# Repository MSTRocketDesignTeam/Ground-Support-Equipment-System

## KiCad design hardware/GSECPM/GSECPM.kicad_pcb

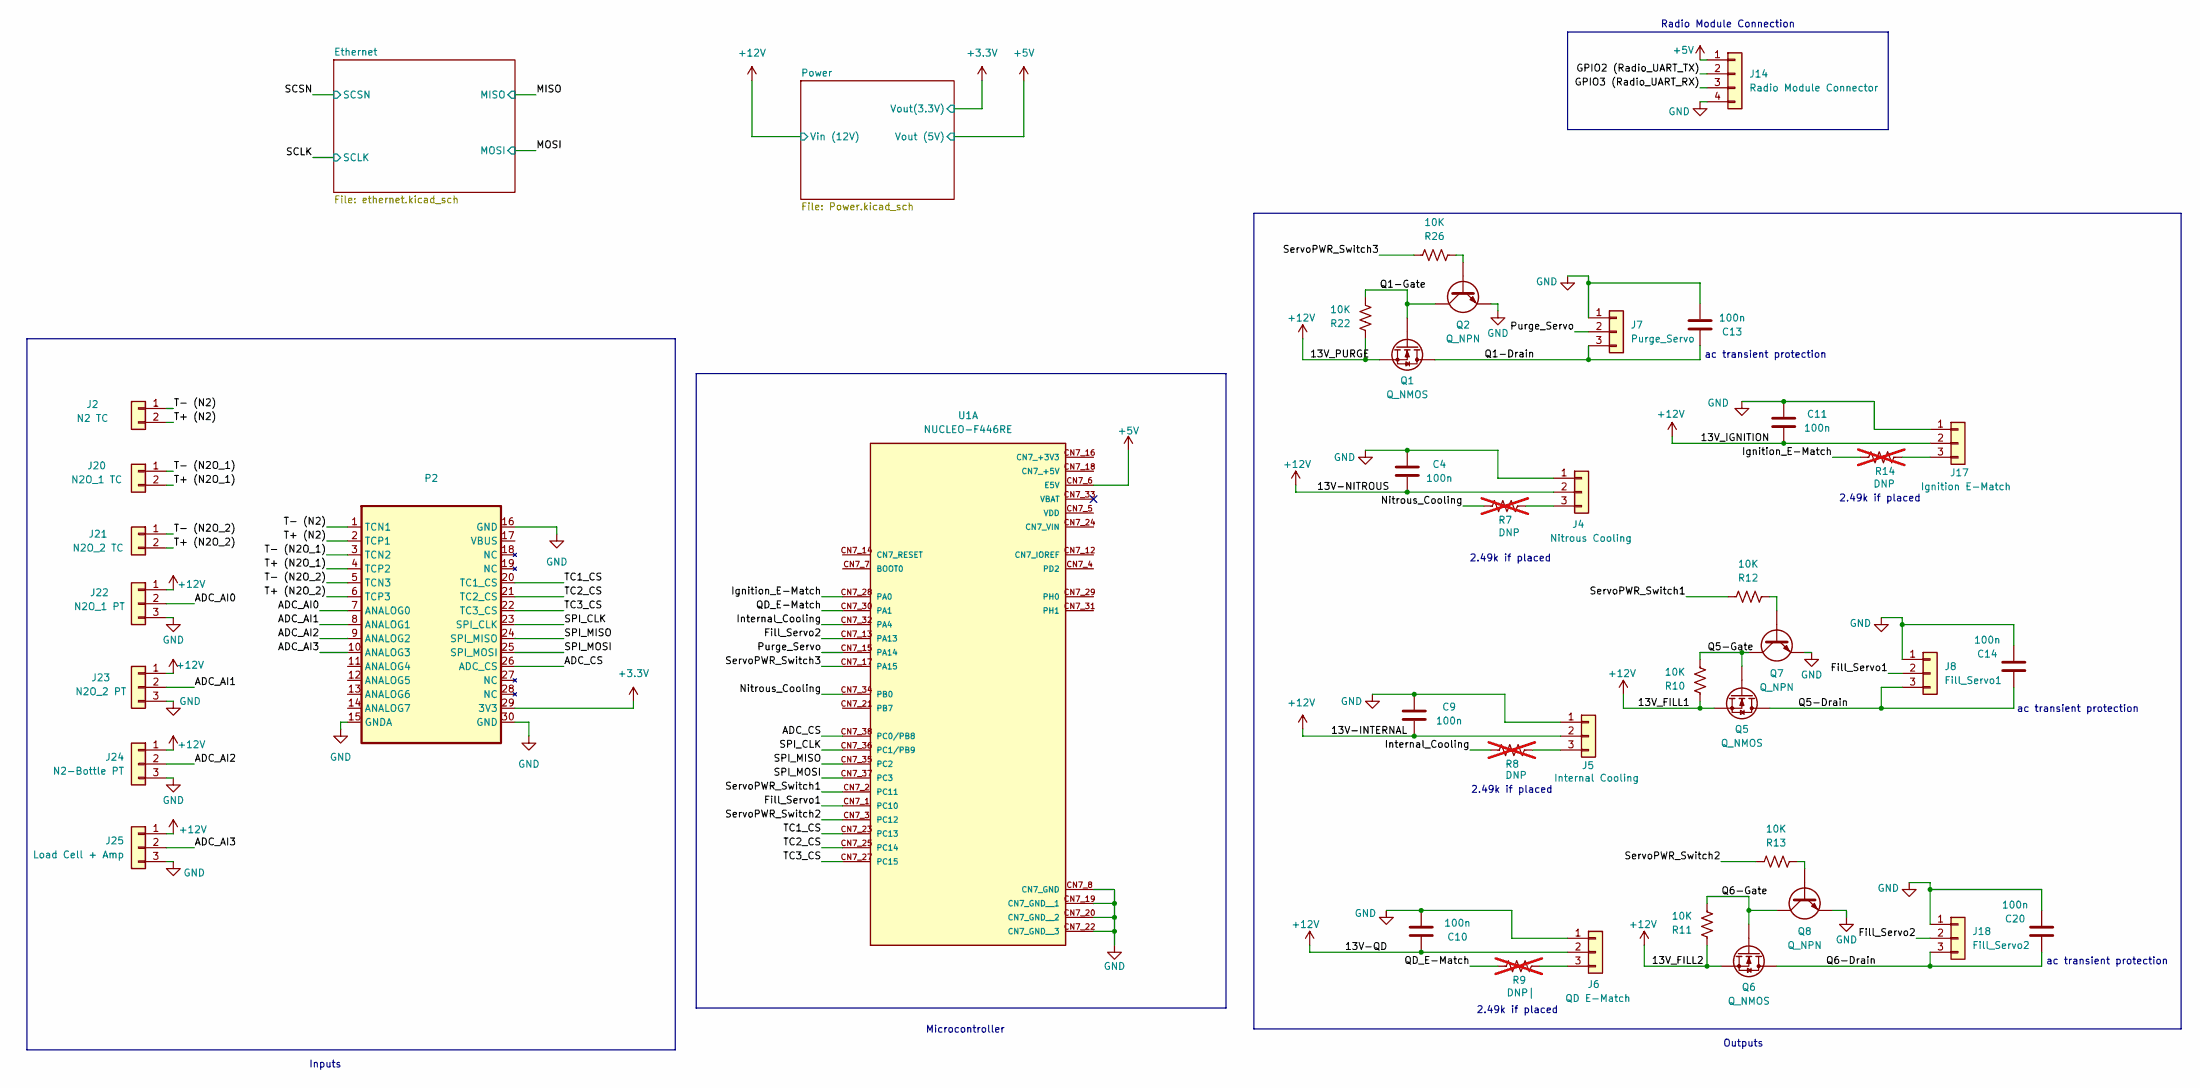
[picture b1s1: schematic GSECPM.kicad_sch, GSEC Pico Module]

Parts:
C4, C9, C10, C11, C13, C14, C20: 100n; C_0603_1608Metric
J2: N2 TC; TerminalBlock_Xinya_XY308-2.54-2P_1x02_P2.54mm_Horizontal
J4: Nitrous Cooling; PinHeader_1x03_P2.54mm_Vertical
J5: Internal Cooling; PinHeader_1x03_P2.54mm_Vertical
J6: QD E-Match; PinHeader_1x03_P2.54mm_Vertical
J7: Purge_Servo; TerminalBlock_Xinya_XY308-2.54-3P_1x03_P2.54mm_Horizontal
J8: Fill_Servo1; TerminalBlock_Xinya_XY308-2.54-3P_1x03_P2.54mm_Horizontal
J14: Radio Module Connector; PinHeader_1x04_P2.54mm_Vertical
J17: Ignition E-Match; PinHeader_1x03_P2.54mm_Vertical
J18: Fill_Servo2; TerminalBlock_Xinya_XY308-2.54-3P_1x03_P2.54mm_Horizontal
J20: N2O_1 TC; TerminalBlock_Xinya_XY308-2.54-2P_1x02_P2.54mm_Horizontal
J21: N2O_2 TC; TerminalBlock_Xinya_XY308-2.54-2P_1x02_P2.54mm_Horizontal
J22: N2O_1 PT; TerminalBlock_Xinya_XY308-2.54-3P_1x03_P2.54mm_Horizontal
J23: N2O_2 PT; TerminalBlock_Xinya_XY308-2.54-3P_1x03_P2.54mm_Horizontal
J24: N2-Bottle PT; TerminalBlock_Xinya_XY308-2.54-3P_1x03_P2.54mm_Horizontal
J25: Load Cell + Amp; TerminalBlock_Xinya_XY308-2.54-3P_1x03_P2.54mm_Horizontal
P2: DAQBoard V1
Q1, Q5, Q6: Q_NMOS; SOT-223_3P7X6P7_ONS
Q2, Q7, Q8: Q_NPN; SOT-323_SC-70
R7, R8, R14: DNP; R_0603_1608Metric; not fitted
R9: DNP|; R_0603_1608Metric; not fitted
R10, R11, R12, R13, R22, R26: 10K; R_0603_1608Metric
U1: NUCLEO-F446RE; MODULE_NUCLEO-F446RE; MPN NUCLEO-F446RE

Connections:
+3.3V: P2.29 (3V3); also elsewhere on the board
+5V: J14.1, U1.CN7_6 (E5V); also elsewhere on the board
+12V: C4.1, C9.1, C10.1, C11.1, J4.2, J5.2, J6.2, J17.2, J22.1, J23.1, J24.1, J25.1, Q1.3 (S), Q5.3 (S), Q6.3 (S), R10.2, R11.2, R22.2; also elsewhere on the board
/ADC_AI0: J22.2, P2.7 (ANALOG0)
/ADC_AI1: J23.2, P2.8 (ANALOG1)
/ADC_AI2: J24.2, P2.9 (ANALOG2)
/ADC_AI3: J25.2, P2.10 (ANALOG3)
/ADC_CS: P2.26 (ADC_CS), U1.CN7_38 (PC0/PB8)
/Fill_Servo1: J8.2, U1.CN7_1 (PC10)
/Fill_Servo2: J18.2, U1.CN7_13 (PA13)
/GPIO2 (Radio_UART_TX): J14.2
/GPIO3 (Radio_UART_RX): J14.3
/Ignition_E-Match: R14.1, U1.CN7_28 (PA0)
/Internal_Cooling: R8.1, U1.CN7_32 (PA4)
/Nitrous_Cooling: R7.1, U1.CN7_34 (PB0)
/Purge_Servo: J7.2, U1.CN7_15 (PA14)
/Q1-Drain: C13.1, J7.3, Q1.2 (D)
/Q1-Gate: Q1.1 (G), Q2.3 (C), R22.1
/Q5-Drain: C14.1, J8.3, Q5.2 (D)
/Q5-Gate: Q5.1 (G), Q7.3 (C), R10.1
/Q6-Drain: C20.1, J18.3, Q6.2 (D)
/Q6-Gate: Q6.1 (G), Q8.3 (C), R11.1
/QD_E-Match: R9.1, U1.CN7_30 (PA1)
/SPI_CLK: P2.23 (SPI_CLK), U1.CN7_36 (PC1/PB9)
/SPI_MISO: P2.24 (SPI_MISO), U1.CN7_35 (PC2)
/SPI_MOSI: P2.25 (SPI_MOSI), U1.CN7_37 (PC3)
/ServoPWR_Switch1: R12.2, U1.CN7_2 (PC11)
/ServoPWR_Switch2: R13.2, U1.CN7_3 (PC12)
/ServoPWR_Switch3: R26.2, U1.CN7_17 (PA15)
/T+ (N2): J2.2, P2.2 (TCP1)
/T+ (N2O_1): J20.2, P2.4 (TCP2)
/T+ (N2O_2): J21.2, P2.6 (TCP3)
/T- (N2): J2.1, P2.1 (TCN1)
/T- (N2O_1): J20.1, P2.3 (TCN2)
/T- (N2O_2): J21.1, P2.5 (TCN3)
/TC1_CS: P2.20 (TC1_CS), U1.CN7_23 (PC13)
/TC2_CS: P2.21 (TC2_CS), U1.CN7_25 (PC14)
/TC3_CS: P2.22 (TC3_CS), U1.CN7_27 (PC15)
GND: C4.2, C9.2, C10.2, C11.2, C13.2, C14.2, C20.2, J4.1, J5.1, J6.1, J7.1, J8.1, J14.4, J17.1, J18.1, J22.3, J23.3, J24.3, J25.3, P2.15 (GNDA), P2.16 (GND), P2.30 (GND), Q2.2 (E), Q7.2 (E), Q8.2 (E), U1.CN7_8 (CN7_GND), U1.CN7_19 (CN7_GND__1), U1.CN7_20 (CN7_GND__2), U1.CN7_22 (CN7_GND__3); also elsewhere on the board
unnamed: J4.3, R7.2
unnamed: J5.3, R8.2
unnamed: J6.3, R9.2
unnamed: J17.3, R14.2
unnamed: Q2.1 (B), R26.1
unnamed: Q7.1 (B), R12.1
unnamed: Q8.1 (B), R13.1

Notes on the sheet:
Outputs
ac transient protection
2.49k if placed
Radio Module Connection
Inputs
Microcontroller

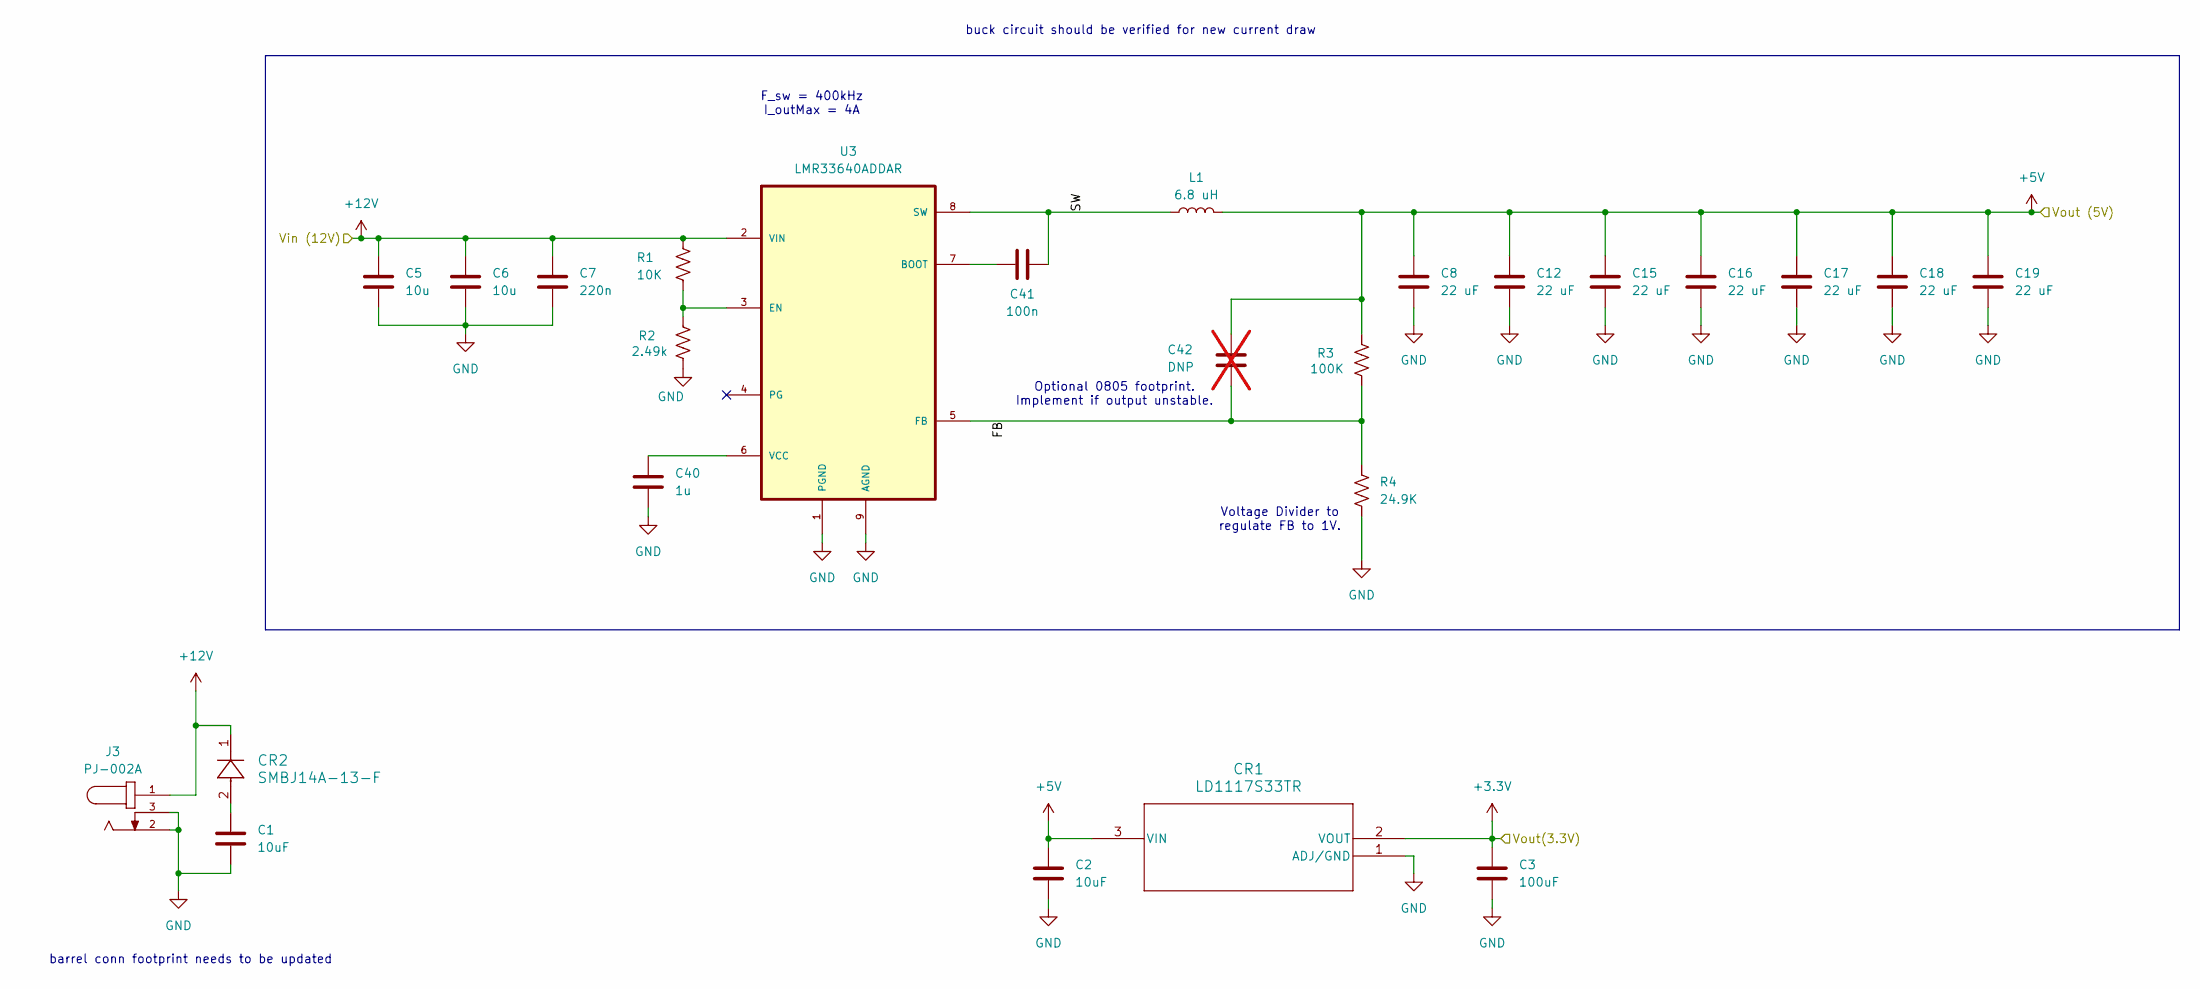
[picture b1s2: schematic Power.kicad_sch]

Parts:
C1, C2: 10uF; C_0603_1608Metric
C3: 100uF; C_1206_3216Metric
C5, C6: 10u; C_1210_3225Metric
C7: 220n; C_0805_2012Metric
C8, C12, C15, C16, C17, C18, C19: 22 uF; C_0805_2012Metric
C40: 1u; C_0805_2012Metric
C41: 100n; C_0603_1608Metric
C42: DNP; C_0805_2012Metric; not fitted
CR1: LD1117S33TR; SOT-223_STM
CR2: SMBJ14A-13-F; SMB_DIO
J3: PJ-002A; CUI_PJ-002A; MPN PJ-002A
L1: 6.8 uH; IND_BOURNS_SRR1260
R1: 10K; R_0603_1608Metric
R2: 2.49k; R_0603_1608Metric
R3: 100K; R_1210_3225Metric
R4: 24.9K; R_1210_3225Metric
U3: LMR33640ADDAR; Texas_HSOP-8-1EP_3.9x4.9mm_P1.27mm_ThermalVias

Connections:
+3.3V: C3.1, CR1.2 (VOUT); also elsewhere on the board
+5V: C2.1, C8.1, C12.1, C15.1, C16.1, C17.1, C18.1, C19.1, C42.2, CR1.3 (VIN), L1.2, R3.2; also elsewhere on the board
+12V: C5.1, C6.1, C7.1, CR2.1, J3.1, R1.1, U3.2 (VIN); also elsewhere on the board
/Power/FB: C42.1, R3.1, R4.1, U3.5 (FB)
/Power/SW: C41.2, L1.1, U3.8 (SW)
GND: C1.2, C2.2, C3.2, C5.2, C6.2, C7.2, C8.2, C12.2, C15.2, C16.2, C17.2, C18.2, C19.2, C40.2, CR1.1 (ADJ/GND), J3.2, J3.3, R2.1, R4.2, U3.1 (PGND), U3.9 (AGND); also elsewhere on the board
unnamed: C1.1, CR2.2
unnamed: C41.1, U3.7 (BOOT)
unnamed: R1.2, R2.2, U3.3 (EN)
unnamed: C40.1, U3.6 (VCC)

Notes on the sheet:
F_sw = 400kHz I_outMax = 4A
Optional 0805 footprint. Implement if output unstable.
Voltage Divider to regulate FB to 1V.
buck circuit should be verified for new current draw
barrel conn footprint needs to be updated

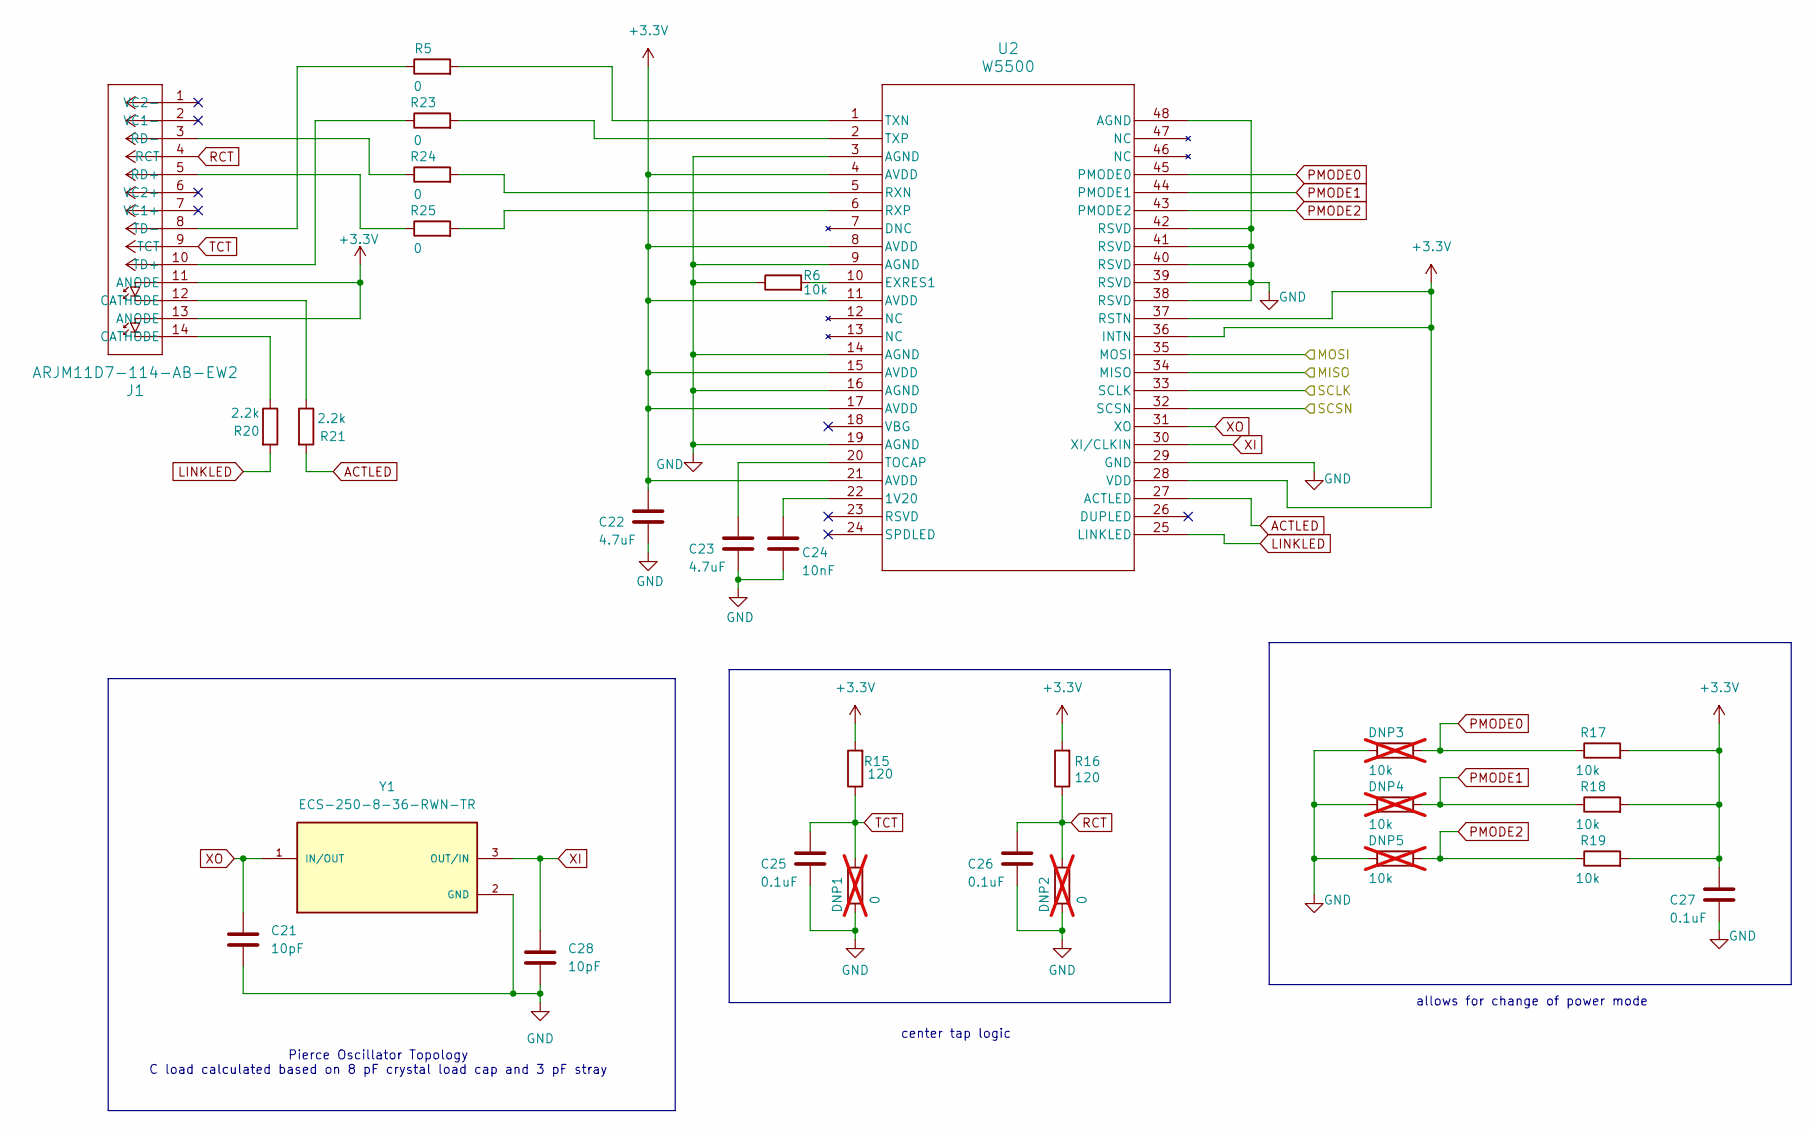
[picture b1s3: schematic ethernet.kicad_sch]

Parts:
C21, C28: 10pF; C_0603_1608Metric
C22, C23: 4.7uF; C_0603_1608Metric
C24: 10nF; C_0603_1608Metric
C25, C26, C27: 0.1uF; C_0603_1608Metric
DNP1, DNP2: 0; R_0805_2012Metric; not fitted
DNP3, DNP4, DNP5: 10k; R_0805_2012Metric; not fitted
J1: ARJM11D7-114-AB-EW2; CONN_ARJM11D7-114-AB-EW2_ABR
R5, R23, R24, R25: 0; R_0603_1608Metric
R6, R17, R18, R19: 10k; R_0603_1608Metric
R15, R16: 120; R_0603_1608Metric
R20, R21: 2.2k; R_0603_1608Metric
U2: W5500; 48LQFP_W5500_WIZ
Y1: ECS-250-8-36-RWN-TR; XTAL_ECS-250-8-36-RWN-TR; PARTREV 2017

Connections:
+3.3V: C22.1, C27.1, J1.11 (ANODE), J1.13 (ANODE), R15.2, R16.2, R17.2, R18.2, R19.2, U2.4 (AVDD), U2.8 (AVDD), U2.11 (AVDD), U2.15 (AVDD), U2.17 (AVDD), U2.21 (AVDD), U2.28 (VDD), U2.36 (INTN), U2.37 (RSTN); also elsewhere on the board
/MISO: U2.34 (MISO)
/MOSI: U2.35 (MOSI)
/SCLK: U2.33 (SCLK)
/SCSN: U2.32 (SCSN)
ACTLED: R21.2, U2.27 (ACTLED)
GND: C21.2, C22.2, C23.2, C24.2, C25.2, C26.2, C27.2, C28.2, DNP1.1, DNP2.1, DNP3.1, DNP4.1, DNP5.1, R6.1, U2.3 (AGND), U2.9 (AGND), U2.14 (AGND), U2.16 (AGND), U2.19 (AGND), U2.29 (GND), U2.38 (RSVD), U2.39 (RSVD), U2.40 (RSVD), U2.41 (RSVD), U2.42 (RSVD), U2.48 (AGND), Y1.2 (GND); also elsewhere on the board
LINKLED: R20.2, U2.25 (LINKLED)
unnamed: J1.12 (CATHODE), R21.1
unnamed: J1.14 (CATHODE), R20.1
unnamed: J1.5 (RD+), R25.1
unnamed: J1.3 (RD-), R24.1
unnamed: J1.10 (TD+), R23.1
unnamed: J1.8 (TD-), R5.1
unnamed: C24.1, U2.22 (1V20)
unnamed: R6.2, U2.10 (EXRES1)
unnamed: R24.2, U2.5 (RXN)
unnamed: R25.2, U2.6 (RXP)
unnamed: C23.1, U2.20 (TOCAP)
unnamed: R5.2, U2.1 (TXN)
unnamed: R23.2, U2.2 (TXP)
PMODE0: DNP3.2, R17.1, U2.45 (PMODE0)
PMODE1: DNP4.2, R18.1, U2.44 (PMODE1)
PMODE2: DNP5.2, R19.1, U2.43 (PMODE2)
RCT: C26.1, DNP2.2, J1.4 (RCT), R16.1
TCT: C25.1, DNP1.2, J1.9 (TCT), R15.1
XI: C28.1, U2.30 (XI/CLKIN), Y1.3 (OUT/IN)
XO: C21.1, U2.31 (XO), Y1.1 (IN/OUT)

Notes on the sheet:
Pierce Oscillator Topology C load calculated based on 8 pF crystal load cap and 3 pF stray
center tap logic
allows for change of power mode

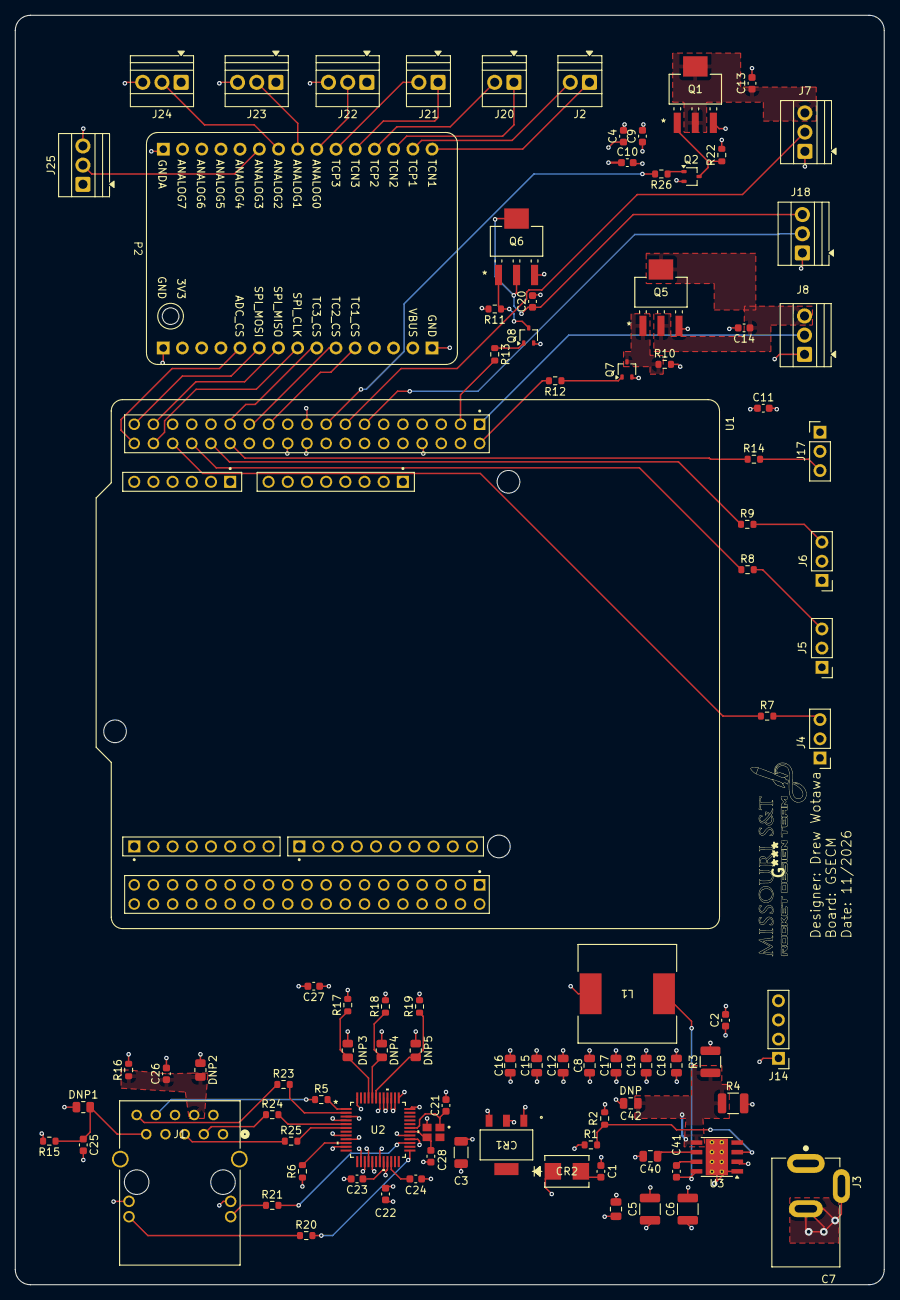
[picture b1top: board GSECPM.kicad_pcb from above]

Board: 4 copper layers, 115.0 x 168.0 mm, 93 parts (0 on the bottom side), 72 nets.

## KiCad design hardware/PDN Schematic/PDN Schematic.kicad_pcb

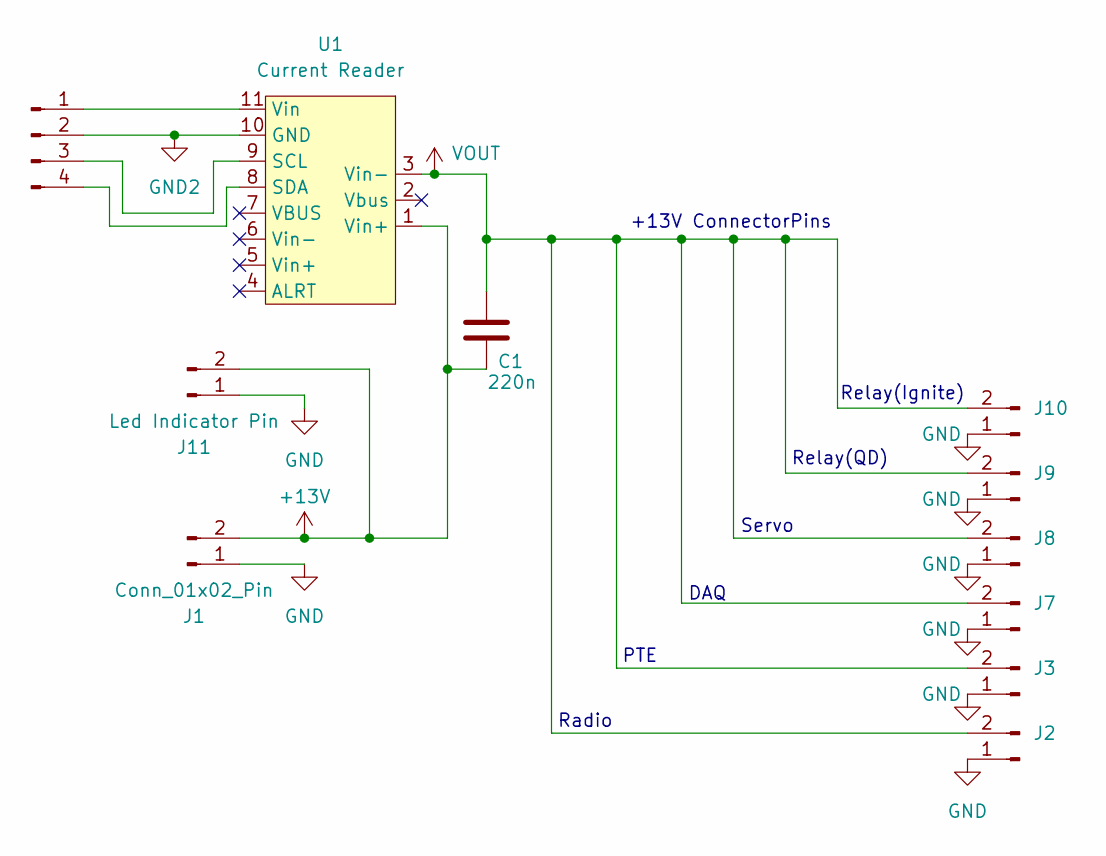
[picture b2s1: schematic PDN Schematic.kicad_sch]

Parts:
C1: 220n; C_0805_2012Metric; DigiKey Digikey: https://www.digikey.com/en/pro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
J1: Conn_01x02_Pin; AMASS_XT60-M_1x02_P7.20mm_Vertical
J2, J3, J7, J8, J9, J10: Conn_01x02_Pin; AMASS_XT30U-M_1x02_P5.0mm_Vertical
J4: Conn_01x04_Pin; PinHeader_1x04_P2.54mm_Vertical
J11: Led Indicator Pin; AMASS_XT30U-M_1x02_P5.0mm_Vertical
U1: Current Reader; INA238_MODULE

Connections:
+13V: C1.2, J1.2, J11.2, U1.1 (Vin+)
GND: J1.1, J2.1, J3.1, J7.1, J8.1, J9.1, J10.1, J11.1
GND2: J4.2, U1.10 (GND)
unnamed: J4.1, U1.11 (Vin)
unnamed: J4.3, U1.9 (SCL)
unnamed: J4.4, U1.8 (SDA)
VOUT: C1.1, J2.2, J3.2, J7.2, J8.2, J9.2, J10.2, U1.3 (Vin-)

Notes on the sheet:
Relay(Ignite)
Servo
Radio
Relay(QD)
+13V ConnectorPins
DAQ
PTE

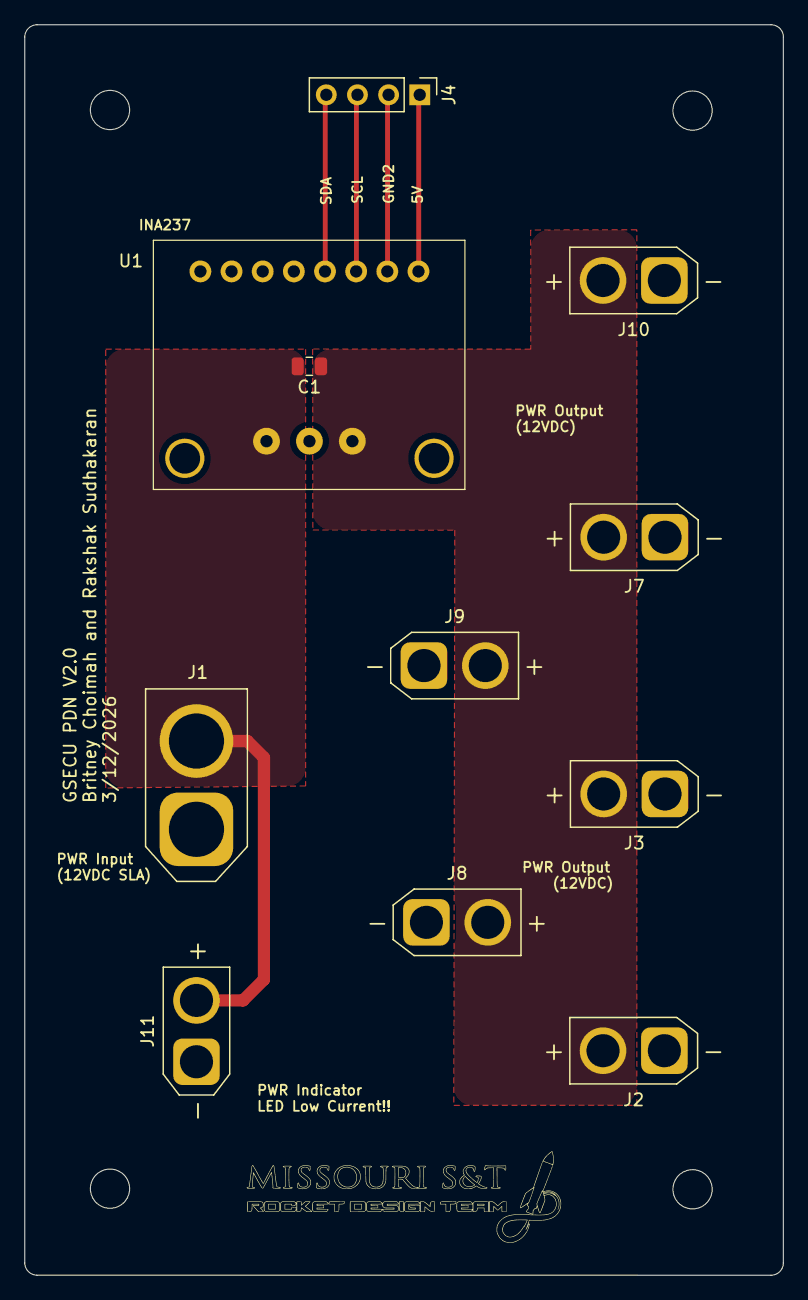
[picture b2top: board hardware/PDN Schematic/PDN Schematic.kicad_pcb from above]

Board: 2 copper layers, 61.9 x 102.0 mm, 11 parts (0 on the bottom side), 7 nets.

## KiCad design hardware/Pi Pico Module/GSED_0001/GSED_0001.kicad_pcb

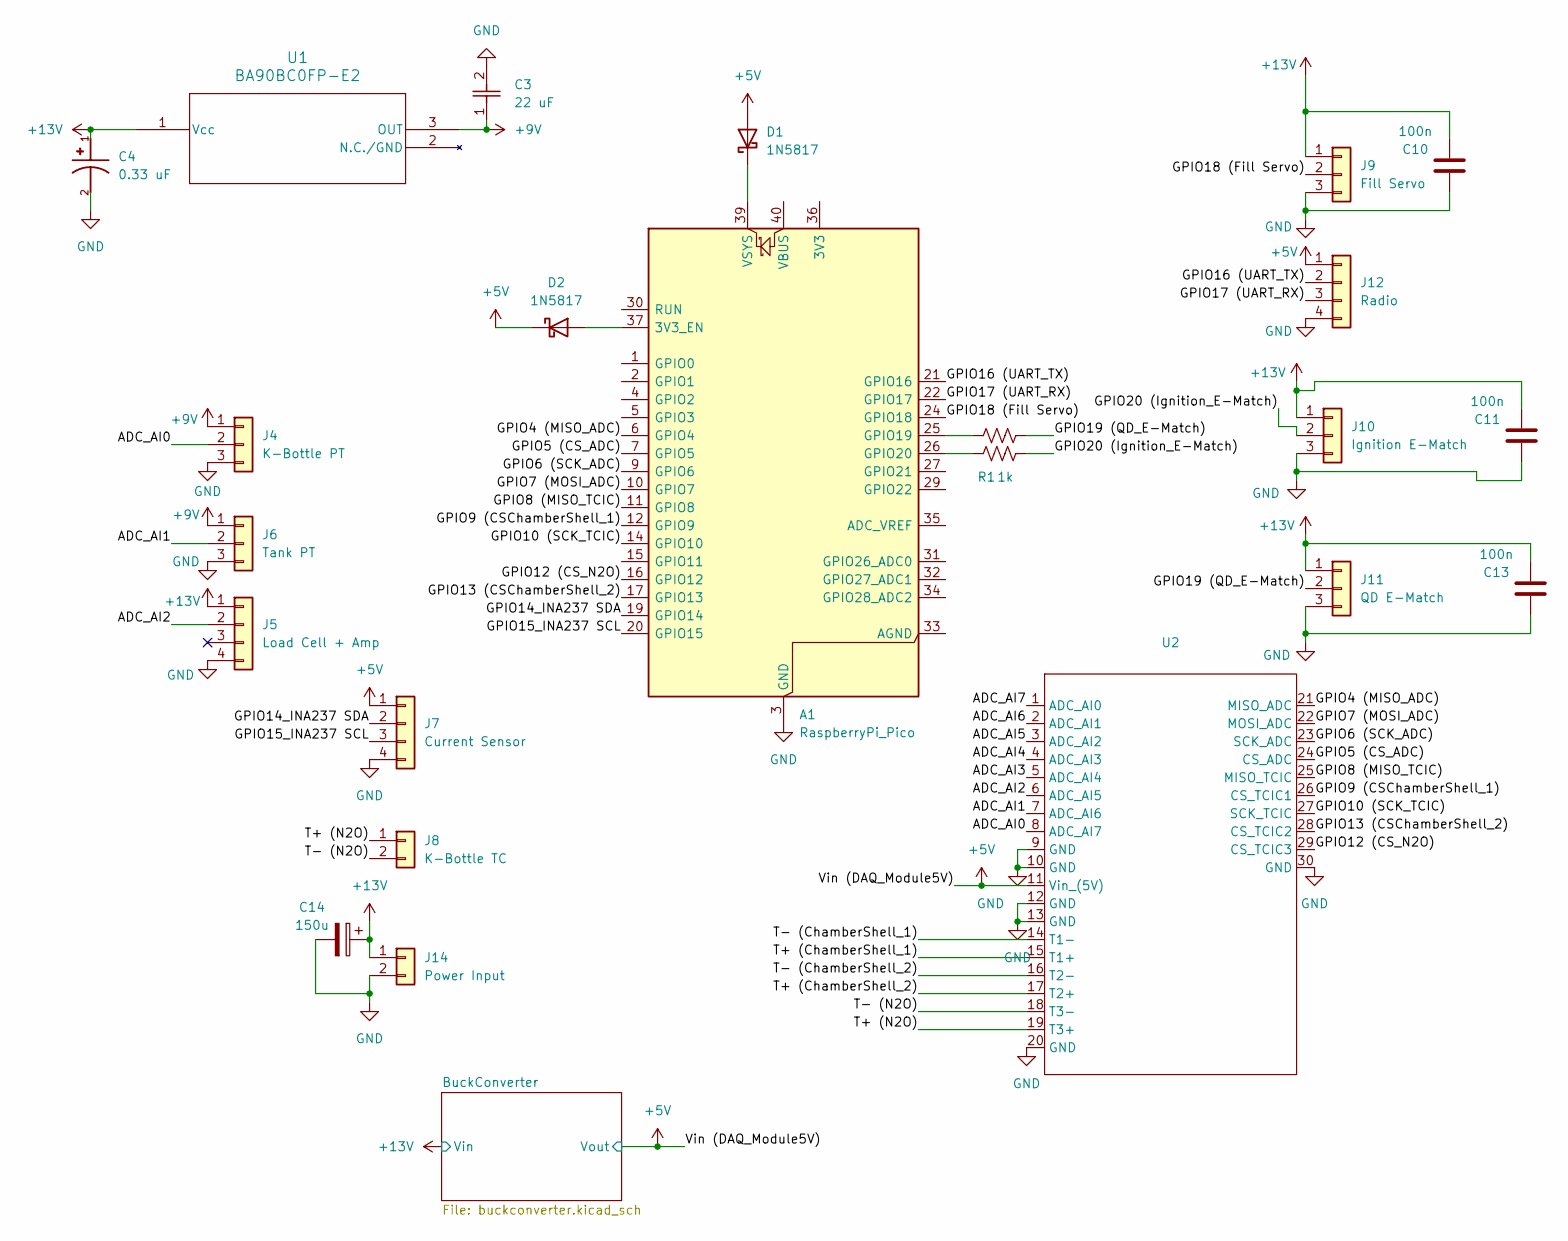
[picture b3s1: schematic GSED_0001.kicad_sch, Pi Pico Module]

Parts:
A1: RaspberryPi_Pico; RaspberryPi_Pico_Common_Unspecified
C3: 22 uF; C_0805_2012Metric
C4: 0.33 uF; CAPMP3216X180N; PARTREV 031320
C10, C11, C13: 100n; C_0603_1608Metric
C14: 150u; CAPPRD500W60D1000H1600
D1, D2: 1N5817; D_DO-41_SOD81_P10.16mm_Horizontal
J4: K-Bottle PT; PinHeader_1x03_P2.54mm_Vertical
J5: Load Cell + Amp; PinHeader_1x04_P2.54mm_Vertical
J6: Tank PT; PinHeader_1x03_P2.54mm_Vertical
J7: Current Sensor; PinHeader_1x04_P2.54mm_Vertical
J8: K-Bottle TC; AMKPCB
J9: Fill Servo; PinHeader_1x03_P2.54mm_Vertical
J10: Ignition E-Match; PinHeader_1x03_P2.54mm_Vertical
J11: QD E-Match; PinHeader_1x03_P2.54mm_Vertical
J12: Radio; PinHeader_1x04_P2.54mm_Vertical
J14: Power Input; AMASS_XT30U-M_1x02_P5.0mm_Vertical
R1, R2: 1k; R_0603_1608Metric
U1: BA90BC0FP-E2; TO252-3_ROM
U2: DAQ_Module

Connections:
+5V: D1.2 (A), D2.1 (K), J7.1, J12.1, U2.11 (Vin_(5V)); also elsewhere on the board
+9V: C3.1, J4.1, J6.1, U1.3 (OUT)
+13V: C4.1, C10.2, C11.2, C13.2, C14.1, J5.1, J9.1, J10.1, J11.1, J14.1, U1.1 (Vcc); also elsewhere on the board
/ADC_AI0: J4.2, U2.8 (ADC_AI7)
/ADC_AI1: J6.2, U2.7 (ADC_AI6)
/ADC_AI2: J5.2, U2.6 (ADC_AI5)
/ADC_AI3: U2.5 (ADC_AI4)
/ADC_AI4: U2.4 (ADC_AI3)
/ADC_AI5: U2.3 (ADC_AI2)
/ADC_AI6: U2.2 (ADC_AI1)
/ADC_AI7: U2.1 (ADC_AI0)
/GPIO4 (MISO_ADC): A1.6 (GPIO4), U2.21 (MISO_ADC)
/GPIO5 (CS_ADC): A1.7 (GPIO5), U2.24 (CS_ADC)
/GPIO6 (SCK_ADC): A1.9 (GPIO6), U2.23 (SCK_ADC)
/GPIO7 (MOSI_ADC): A1.10 (GPIO7), U2.22 (MOSI_ADC)
/GPIO8 (MISO_TCIC): A1.11 (GPIO8), U2.25 (MISO_TCIC)
/GPIO9 (CSChamberShell_1): A1.12 (GPIO9), U2.26 (CS_TCIC1)
/GPIO10 (SCK_TCIC): A1.14 (GPIO10), U2.27 (SCK_TCIC)
/GPIO12 (CS_N2O): A1.16 (GPIO12), U2.29 (CS_TCIC3)
/GPIO13 (CSChamberShell_2): A1.17 (GPIO13), U2.28 (CS_TCIC2)
/GPIO14_INA237 SDA: A1.19 (GPIO14), J7.2
/GPIO15_INA237 SCL: A1.20 (GPIO15), J7.3
/GPIO16 (UART_TX): A1.21 (GPIO16), J12.2
/GPIO17 (UART_RX): A1.22 (GPIO17), J12.3
/GPIO18 (Fill Servo): A1.24 (GPIO18), J9.2
/GPIO19 (QD_E-Match): J11.2, R2.1
/GPIO20 (Ignition_E-Match): J10.2, R1.1
/T+ (ChamberShell_1): U2.15 (T1+)
/T+ (ChamberShell_2): U2.17 (T2+)
/T+ (N2O): J8.1, U2.19 (T3+)
/T- (ChamberShell_1): U2.14 (T1-)
/T- (ChamberShell_2): U2.16 (T2-)
/T- (N2O): J8.2, U2.18 (T3-)
GND: A1.3 (GND), A1.8 (GND), A1.13 (GND), A1.18 (GND), A1.23 (GND), A1.28 (GND), A1.38 (GND), C3.2, C4.2, C10.1, C11.1, C13.1, C14.2, J4.3, J5.4, J6.3, J7.4, J9.3, J10.3, J11.3, J12.4, J14.2, U2.9 (GND), U2.10 (GND), U2.12 (GND), U2.13 (GND), U2.20 (GND), U2.30 (GND); also elsewhere on the board
unnamed: A1.37 (3V3_EN), D2.2 (A)
unnamed: A1.25 (GPIO19), R2.2
unnamed: A1.26 (GPIO20), R1.2
unnamed: A1.39 (VSYS), D1.1 (K)

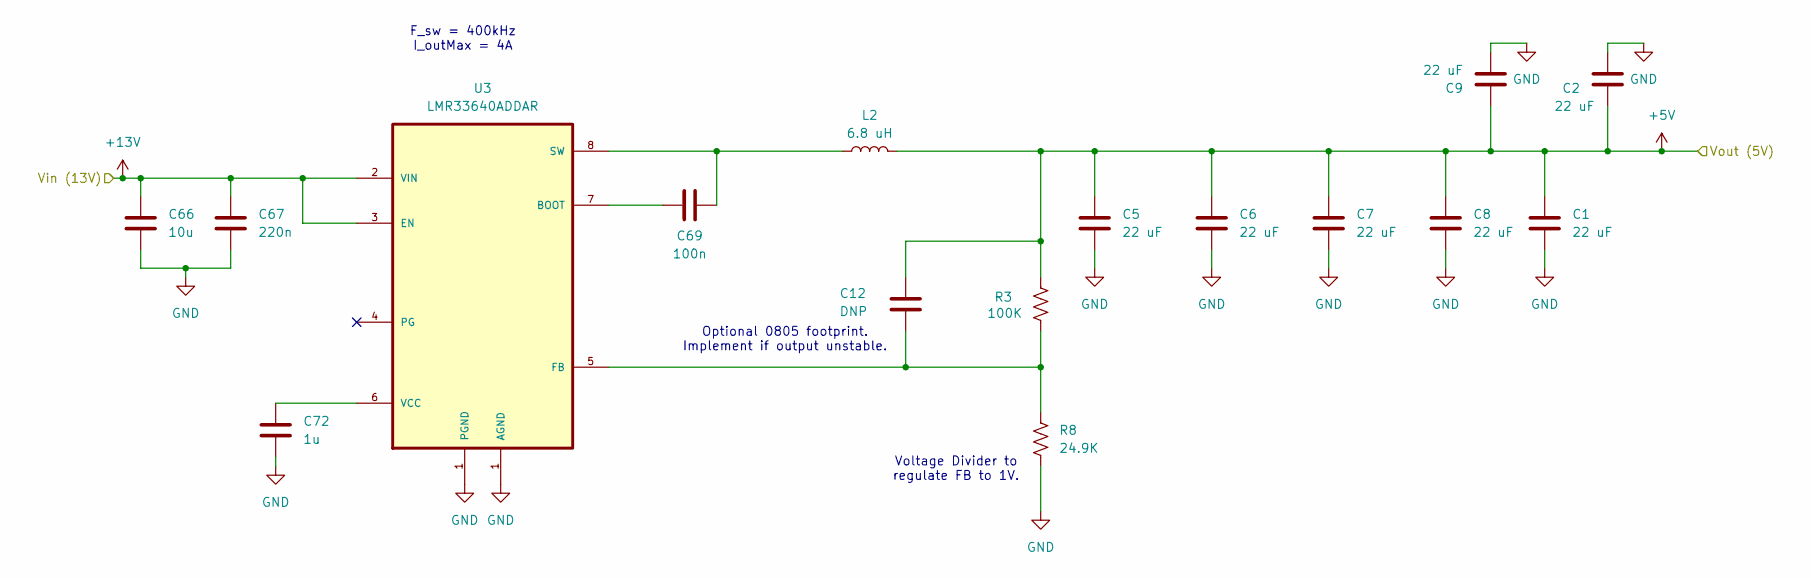
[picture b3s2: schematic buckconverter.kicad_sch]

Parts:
C1, C2, C5, C6, C7, C8, C9: 22 uF; C_0805_2012Metric
C12: DNP; C_0805_2012Metric
C66: 10u; C_0805_2012Metric
C67: 220n; C_0805_2012Metric
C69: 100n; C_0603_1608Metric
C72: 1u; C_0805_2012Metric
L2: 6.8 uH; IND_CSBX0650-6R8M
R3: 100K; R_0603_1608Metric
R8: 24.9K; R_0603_1608Metric
U3: LMR33640ADDAR; Texas_HSOP-8-1EP_3.9x4.9mm_P1.27mm_ThermalVias

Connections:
+5V: C1.1, C2.1, C5.1, C6.1, C7.1, C8.1, C9.1, C12.2, L2.2, R3.2; also elsewhere on the board
+13V: C66.1, C67.1, U3.2 (VIN), U3.3 (EN); also elsewhere on the board
GND: C1.2, C2.2, C5.2, C6.2, C7.2, C8.2, C9.2, C66.2, C67.2, C72.2, R8.2, U3.1 (PGND); also elsewhere on the board
unnamed: C69.1, U3.7 (BOOT)
unnamed: C12.1, R3.1, R8.1, U3.5 (FB)
unnamed: C69.2, L2.1, U3.8 (SW)
unnamed: C72.1, U3.6 (VCC)

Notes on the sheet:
Optional 0805 footprint. Implement if output unstable.
Voltage Divider to regulate FB to 1V.
F_sw = 400kHz I_outMax = 4A

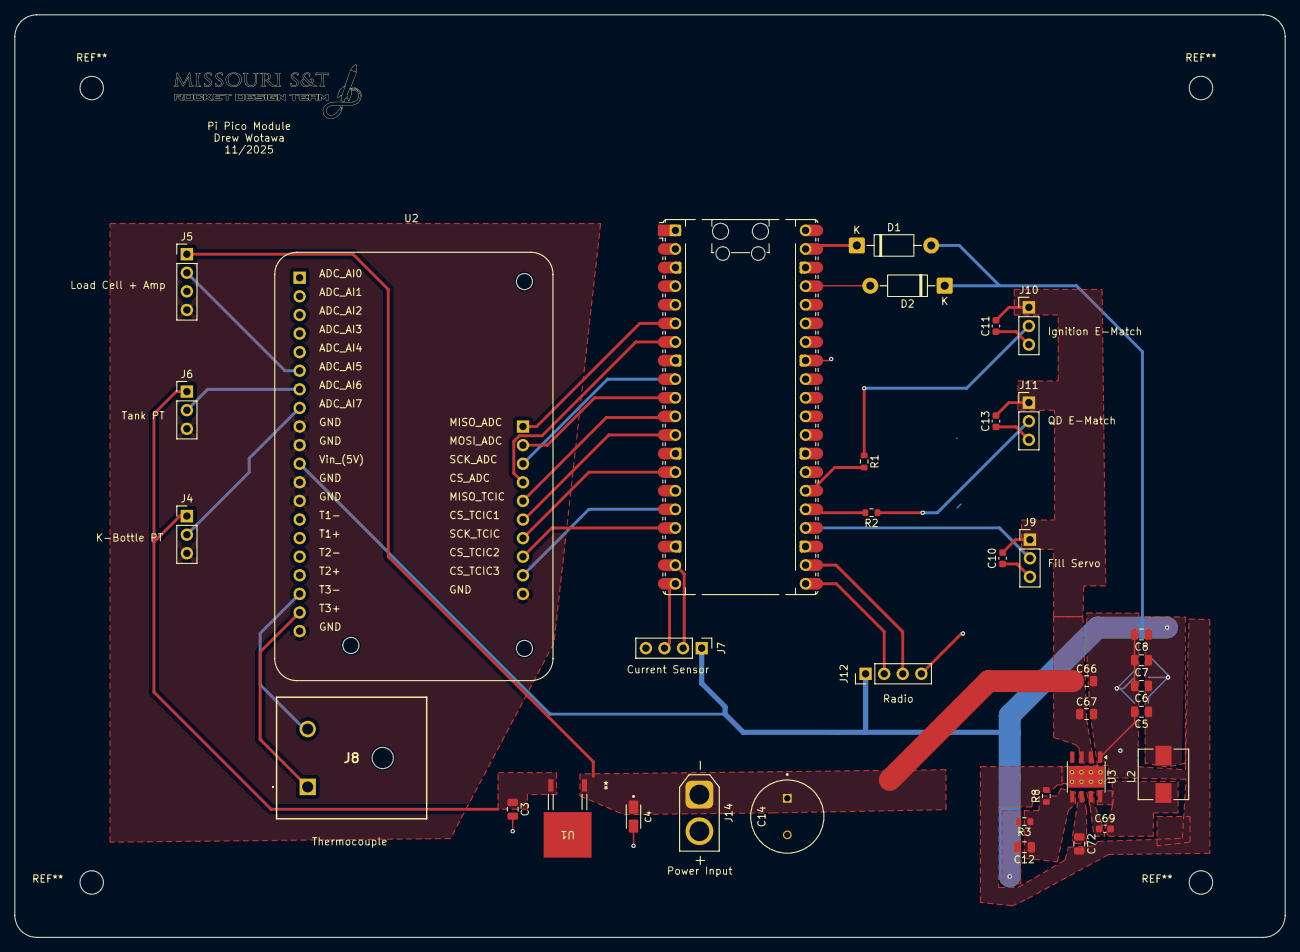
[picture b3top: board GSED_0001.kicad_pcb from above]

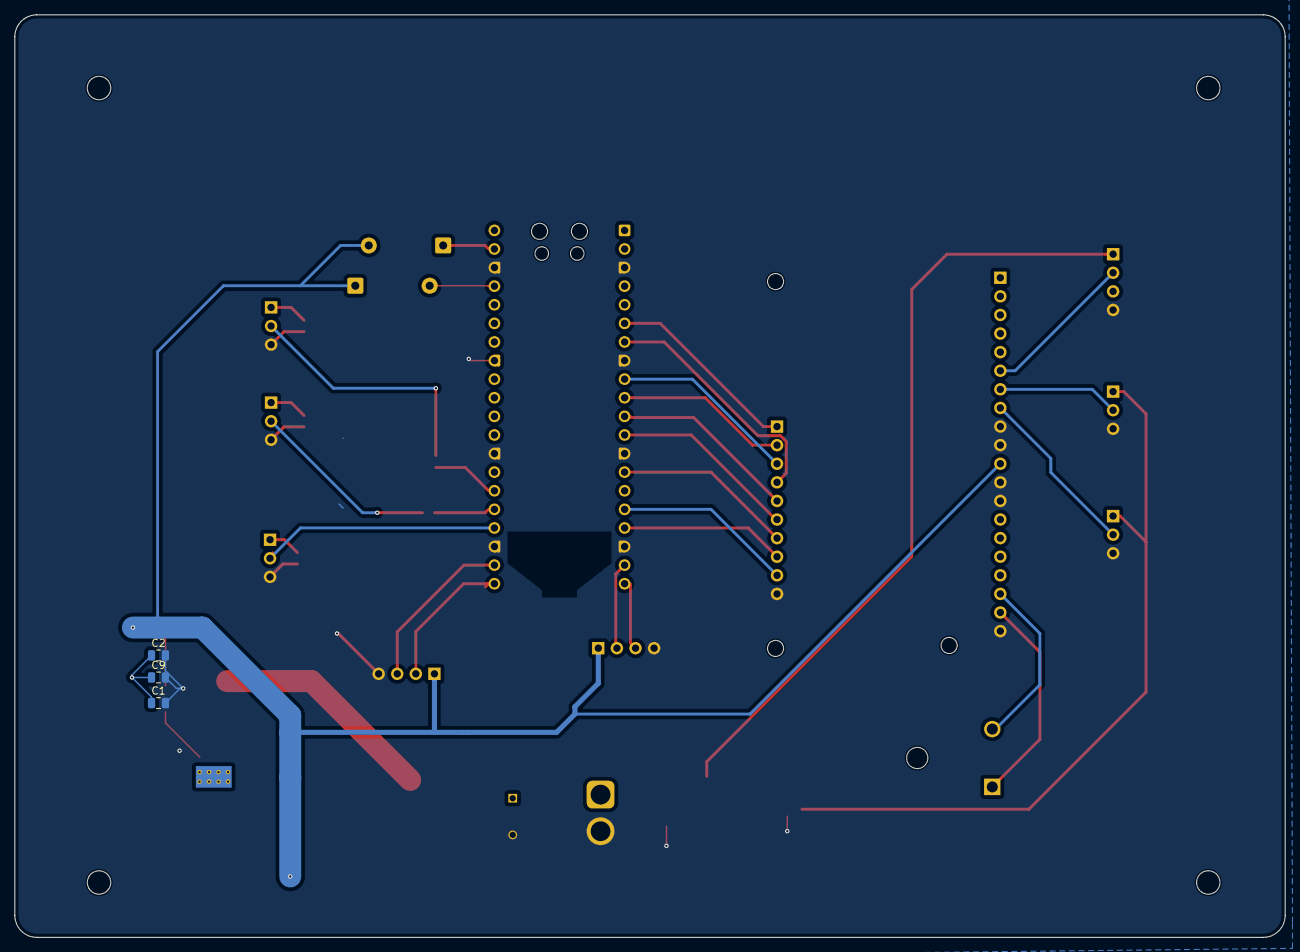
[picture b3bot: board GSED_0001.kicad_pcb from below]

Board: 2 copper layers, 173.5 x 126.0 mm, 39 parts (3 on the bottom side), 33 nets.
